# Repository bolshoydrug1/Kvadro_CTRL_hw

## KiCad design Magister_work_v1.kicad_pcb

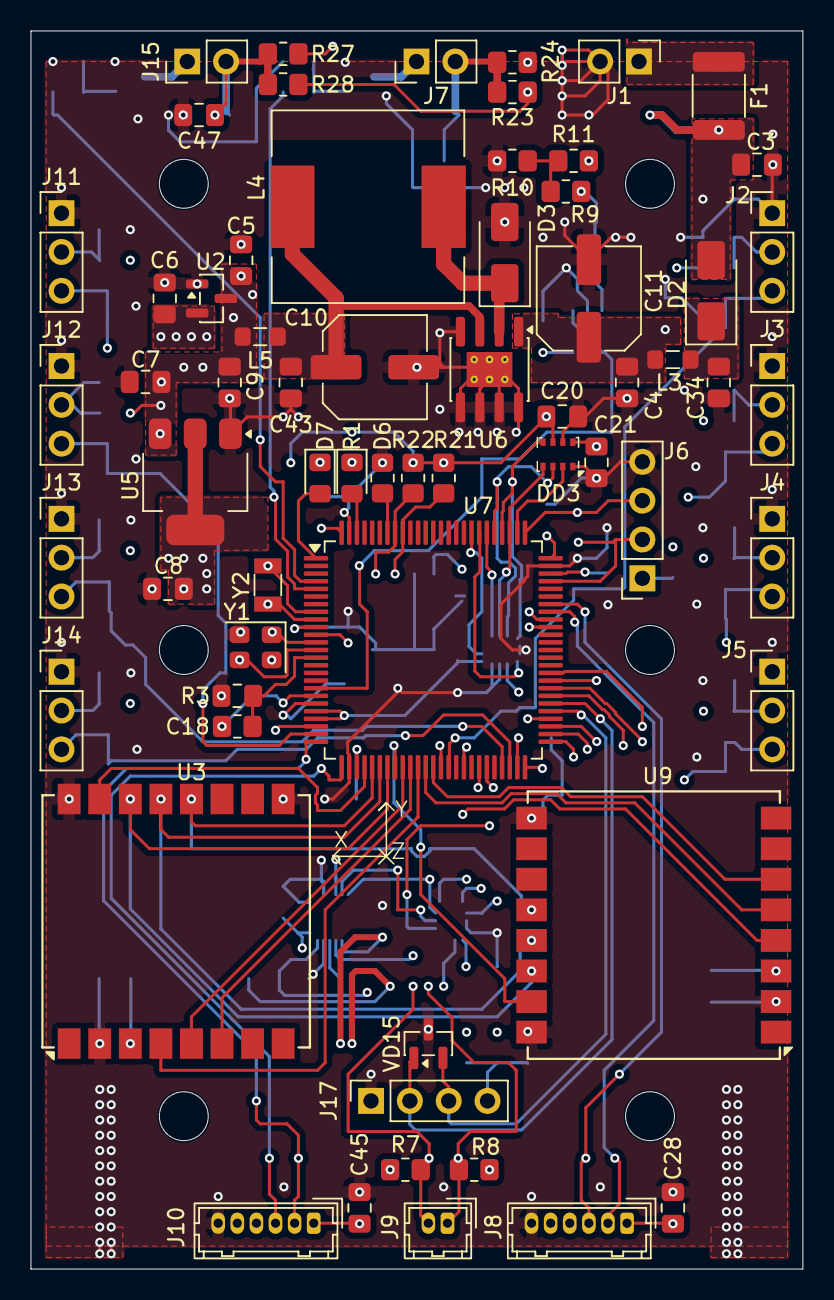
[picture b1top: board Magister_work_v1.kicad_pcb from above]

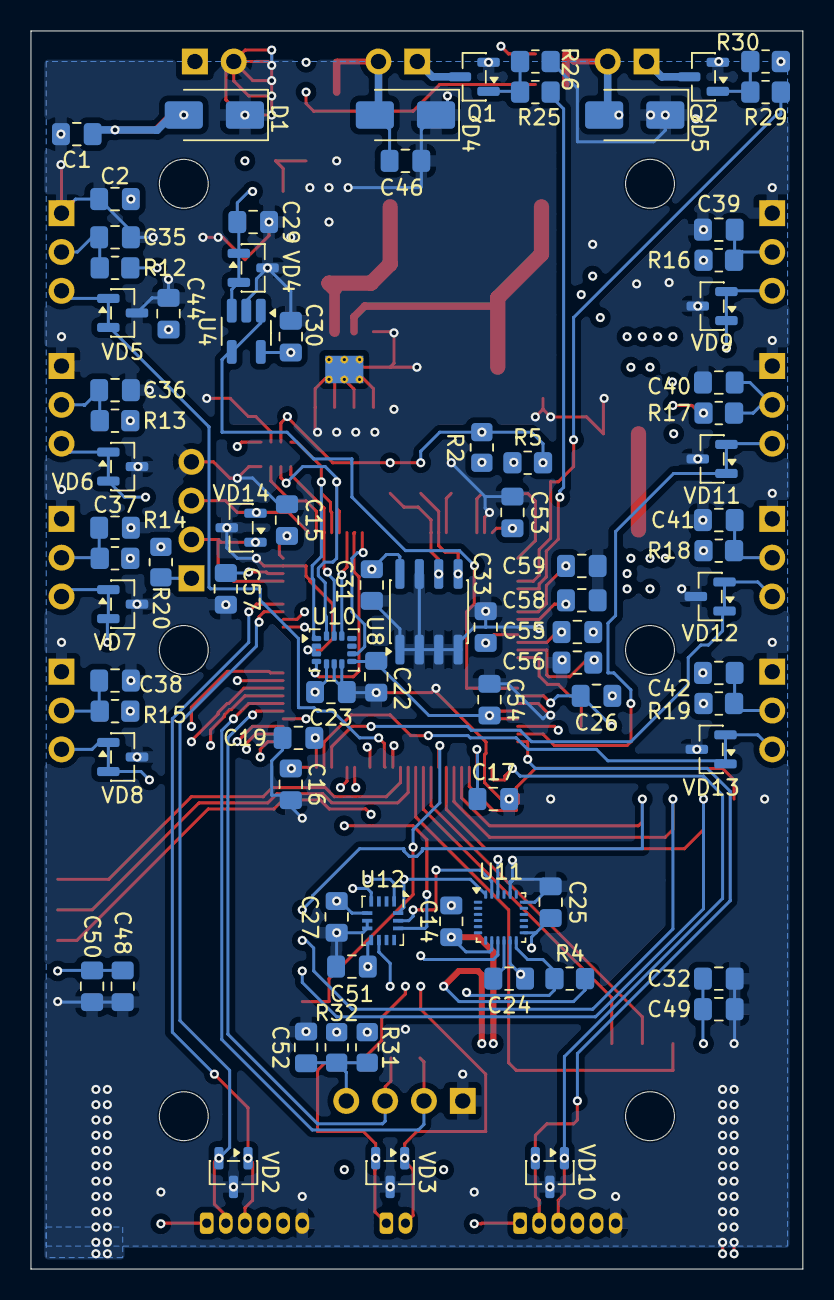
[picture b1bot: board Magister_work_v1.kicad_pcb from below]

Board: 4 copper layers, 50.5 x 81.0 mm, 145 parts (81 on the bottom side), 90 nets.

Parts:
C1: 0.01u; C_0805_2012Metric_Pad1.18x1.45mm_HandSolder
C2, C4, C5, C6, C7, C8, C9, C14, C15, C16, C17, C18, C20, C21, C22, C23, C24, C25, C26, C27, C28, C29, C30, C31, C32, C33, C34, C35, C36, C37, C38, C39, C40, C41, C42, C43, C44, C45, C46, C47, C48, C49, C50, C51, C52, C53, C54: 0.1u; C_0805_2012Metric_Pad1.18x1.45mm_HandSolder
C3: 1u; C_0805_2012Metric_Pad1.18x1.45mm_HandSolder
C10, C11: 100u; C_Elec_6.3x7.7
C19, C57: 2.2u; C_0805_2012Metric_Pad1.18x1.45mm_HandSolder
C55, C56, C58, C59: 15p; C_0805_2012Metric_Pad1.18x1.45mm_HandSolder
D1, D4, D5: SMAJ30CA; D_SMA
D2, D3: SS36; D_SMA
D6, D7: LED; LED_0805_2012Metric_Pad1.15x1.40mm_HandSolder
DD3: BMP280; Bosch_LGA-8_2x2.5mm_P0.65mm_ClockwisePinNumbering
F1: MF-MSMF110-2; Fuse_1812_4532Metric_Pad1.30x3.40mm_HandSolder
J1, J7, J15: Conn_01x02_Pin; PinHeader_1x02_P2.54mm_Vertical
J2, J3, J4, J5, J11, J12, J13, J14: Conn_01x03_Pin; PinHeader_1x03_P2.54mm_Vertical
J6, J17: Conn_01x04_Pin; PinSocket_1x04_P2.54mm_Vertical
J8, J10: Conn_01x06_Pin; Hirose_DF13-06P-1.25DSA_1x06_P1.25mm_Vertical
J9: Conn_01x02_Pin; Hirose_DF13-02P-1.25DSA_1x02_P1.25mm_Vertical
L3, L5: BLM21PG121SN1D; L_0805_2012Metric_Pad1.05x1.20mm_HandSolder
L4: 47uH; L_12x12mm_H8mm
Q1, Q2: AO3400A; SOT-23
R1, R3, R4, R11, R26, R30: 10k; R_0805_2012Metric_Pad1.20x1.40mm_HandSolder
R2, R5: 330; R_0805_2012Metric_Pad1.20x1.40mm_HandSolder
R7, R8, R9, R21, R22: 3k; R_0805_2012Metric_Pad1.20x1.40mm_HandSolder
R10: 1k; R_0805_2012Metric_Pad1.20x1.40mm_HandSolder
R12, R13, R14, R15, R16, R17, R18, R19, R20, R23, R24, R27, R28, R31, R32: 0; R_0805_2012Metric_Pad1.20x1.40mm_HandSolder
R25, R29: 100; R_0805_2012Metric_Pad1.20x1.40mm_HandSolder
U2: XC6206P332MR; SOT-23
U3: Ai-Thinker-Ra-01; Ai-Thinker-Ra-01-LoRa
U4: MCP6001-OT; SOT-23-5_HandSoldering
U5: AMS1117-3.3; SOT-223-3_TabPin2
U6: XL1509-5.0; SOIC-8-1EP_3.9x4.9mm_P1.27mm_EP2.29x3mm_ThermalVias
U7: STM32F407VETx; LQFP-100_14x14mm_P0.5mm
U8: AT24C256; SOIC-8_3.9x4.9mm_P1.27mm
U9: Ai-Thinker-Ra-01SH; Ai-Thinker-Ra-01-LoRa
U10: LSM6DS3; LGA-14_3x2.5mm_P0.5mm_LayoutBorder3x4y
U11: MPU-6500; InvenSense_QFN-24_3x3mm_P0.4mm
U12: BMI270; Bosch_LGA-14_3x2.5mm_P0.5mm
VD2, VD3, VD4, VD5, VD6, VD7, VD8, VD9, VD10, VD11, VD12, VD13, VD14, VD15: GSOT03C-E3-08; SOT-23
Y1: X322525MQB4SI; Oscillator_SMD_Abracon_ASE-4Pin_3.2x2.5mm
Y2: SMD03215C2; Crystal_SMD_3215-2Pin_3.2x1.5mm

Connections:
+3V3A: C6.1, C21.1, C22.1, C25.1, C30.1, C51.2, C54.2, DD3.8 (VDD), U2.2 (VO), U4.5 (V+), U7.21 (VREF+), U7.22 (VDDA), U10.8 (VDD), U11.13 (VDD), U12.8 (VDD)
+3V3D: C8.1, C14.1, C15.1, C16.1, C17.1, C20.1, C23.2, C26.1, C27.1, C31.1, C32.1, C33.1, C48.1, C49.1, C50.1, C53.1, DD3.6 (VDDIO), R2.2, R3.1, R4.2, R5.2, R7.1, R8.1, R20.1, R21.1, R22.1, R31.1, U3.3 (VDD), U5.2 (VO), U7.6 (VBAT), U7.11 (VDD), U7.19 (VDD), U7.28 (VDD), U7.50 (VDD), U7.75 (VDD), U7.100 (VDD), U8.8 (VCC), U9.3 (VDD), U10.5 (VDDIO), U11.8 (VDDIO), U12.5 (VDDIO)
+5V: C5.1, C7.1, C9.1, C28.1, C45.1, J8.1, J10.1, L5.2, R12.2, R13.2, R14.2, R15.2, R16.2, R17.2, R18.2, R19.2, R24.1, R27.1, R32.1, U2.3 (VI), U5.3 (VI)
+12V: C4.1, C11.1, C44.1, L3.2, R9.1, R23.1, R28.1, U6.1 (VIN)
+12V_1: F1.1 (A1), J1.1
+12V_in: C1.1, C2.1, C3.1, D1.2 (A2), D2.2 (A), F1.2 (A2)
/STMF401_Sheet/BOOT0: R1.1, U7.94 (BOOT0)
/STMF401_Sheet/HSE_IN: C55.2, U7.12 (PH0), Y1.1 (OSC)
/STMF401_Sheet/HSE_OUT: C56.1, U7.13 (PH1), Y1.3 (OSC)
/STMF401_Sheet/LSE_IN: C59.1, U7.8 (PC14), Y2.2 (OSC)
/STMF401_Sheet/LSE_OUT: C58.2, U7.9 (PC15), Y2.1 (OSC)
/STMF401_Sheet/RST: C18.1, R3.2, U7.14 (NRST)
/STMF401_Sheet/SWCLK: J6.3, U7.76 (PA14), VD14.2 (K2)
/STMF401_Sheet/SWDIO: J6.2, U7.72 (PA13), VD14.1 (K1)
/STMF401_Sheet/VCAP1: C19.1, U7.49 (VCAP_1)
/STMF401_Sheet/VCAP2: C57.1, U7.73 (VCAP_2)
BAT_CTRL: U4.1, U4.4 (-), U7.18 (PC3)
BMI270_CS: U7.51 (PB12), U12.12 (CSB)
BMI270_INT1: U7.57 (PD10), U12.4 (INT1)
BMI270_INT2: U7.58 (PD11), U12.9 (INT2)
BMI270_SCLK: U7.52 (PB13), U11.23 (SCL/SCLK), U12.13 (SCx)
BMI270_SDI: U7.54 (PB15), U11.24 (SDA/SDI), U12.14 (SDx)
BMI270_SDO: U7.53 (PB14), U11.9 (AD0/SDO), U12.1 (SDO)
BN_880_RX: J8.3, U7.69 (PA10), VD2.1 (K1)
BN_880_SCL: J9.2, R7.2, U7.67 (PA8), VD3.1 (K1)
BN_880_SDA: J9.1, R8.2, U7.66 (PC9), VD3.2 (K2)
BN_880_TX: J8.2, U7.68 (PA9), VD2.2 (K2)
CSB_BMP280: DD3.2 (CSB), U7.77 (PA15)
DEBUG_RX1: J10.3, U7.26 (PA3), VD10.1 (K1)
DEBUG_RX2: J17.2, U7.56 (PD9), VD15.1 (K1)
DEBUG_TX1: J10.2, U7.25 (PA2), VD10.2 (K2)
DEBUG_TX2: J17.3, U7.55 (PD8), VD15.2 (K2)
DIO0_LoRa: U3.5 (DIO0), U7.34 (PC5)
DIO0_RaSH: U7.37 (PB2), U9.5 (DIO0)
DIO1_LoRa: U3.6 (DIO1), U7.35 (PB0)
DIO1_RaSH: U7.38 (PE7), U9.6 (DIO1)
EEPROM_SCL: R21.2, U7.92 (PB6), U8.6 (SCL)
EEPROM_SDA: R22.2, U7.93 (PB7), U8.5 (SDA)
GND: C1.2, C2.2, C3.2, C4.2, C5.2, C6.2, C7.2, C8.2, C9.2, C10.2, C11.2, C14.2, C15.2, C16.2, C17.2, C18.2, C19.2, C20.2, C21.2, C22.2, C23.1, C24.2, C25.2, C26.2, C27.2, C28.2, C29.2, C30.2, C31.2, C32.2, C33.2, C34.2, C35.1, C36.1, C37.1, C38.1, C39.1, C40.1, C41.1, C42.1, C43.2, C44.2, C45.2, C46.2, C47.2, C48.2, C49.2, C50.2, C51.1, C52.2, C53.2, C54.1, C55.1, C56.2, C57.2, C58.1, C59.2, D1.1 (A1), D3.2 (A), D4.1 (A1), D5.1 (A1), DD3.1 (GND), DD3.7 (GND), J1.2, J2.1, J3.1, J4.1, J5.1, J6.4, J8.6, J10.6, J11.1, J12.1, J13.1, J14.1, J17.1, Q1.2 (S), Q2.2 (S), R1.2, R10.2, R26.2, R30.2, U2.1 (GND), U3.2 (GND), U3.9 (GND), U3.16 (GND), U4.2 (V-), U5.1 (GND), U6.4 (~EN), U6.5 (GND), U6.6 (GND), U6.7 (GND), U6.8 (GND), U6.9, U7.10 (VSS), U7.20 (VSSA), U7.27 (VSS), U7.74 (VSS), U7.99 (VSS), U8.1 (A0), U8.2 (A1), U8.3 (A2), U8.4 (GND), U8.7 (WP), U9.2 (GND), U9.9 (GND), U9.16 (GND), U10.2 (SDX), U10.3 (SCX), U10.6 (GND), U10.7 (GND), U11.11 (FSYNC), U11.18 (GND), U11.20 (RESV_GND), U12.6 (GNDIO), U12.7 (GND), VD2.3 (A), VD3.3 (A), VD4.3 (A), VD5.3 (A), VD6.3 (A), VD7.3 (A), VD8.3 (A), VD9.3 (A), VD10.3 (A), VD11.3 (A), VD12.3 (A), VD13.3 (A), VD14.3 (A), VD15.3 (A), Y1.2 (GND), Y1.4 (GND)
LSM_CS: U7.81 (PD0), U10.12 (CS)
LSM_INT1: U7.82 (PD1), U10.4 (INT1)
LSM_INT2: U7.83 (PD2), U10.9 (INT2)
LSM_SCLK: DD3.4 (SCK), U7.78 (PC10), U10.13 (SCL)
LSM_SDI: DD3.3 (SDI), U7.80 (PC12), U10.14 (SDA)
LSM_SDO: DD3.5 (SDO), U7.79 (PC11), U10.1 (SDO/SA0)
MISO_LoRa: U3.13 (MISO), U7.31 (PA6), U9.13 (MISO)
MOSI_LoRa: U3.14 (MOSI), U7.32 (PA7), U9.14 (MOSI)
MPU_CS: U7.59 (PD12), U11.22 (~CS)
MPU_INT: R4.1, U7.60 (PD13), U11.12 (INT)
unnamed: C34.1, D2.1 (K), L3.1
unnamed: D3.1 (K), L4.1, U6.2 (OUT)
unnamed: C46.1, D4.2 (A2), J7.2, R23.2, R24.2
unnamed: C47.1, D5.2 (A2), J15.2, R27.2, R28.2
unnamed: D6.2 (A), U7.98 (PE1)
unnamed: D6.1 (K), R2.1
unnamed: D7.2 (A), U7.1 (PE2)
unnamed: D7.1 (K), R5.1
unnamed: C35.2, J2.2, R12.1
unnamed: C36.2, J3.2, R13.1
unnamed: C37.2, J4.2, R14.1
unnamed: C38.2, J5.2, R15.1
unnamed: J6.1, R20.2
unnamed: J7.1, Q1.3 (D)
unnamed: C39.2, J11.2, R16.1
unnamed: C40.2, J12.2, R17.1
unnamed: C41.2, J13.2, R18.1
unnamed: C42.2, J14.2, R19.1
unnamed: J15.1, Q2.3 (D)
unnamed: C52.1, J17.4, R31.2, R32.2
unnamed: Q1.1 (G), R25.2, R26.1
unnamed: Q2.1 (G), R29.2, R30.1
unnamed: R9.2, R10.1, R11.1
unnamed: C29.1, R11.2, U4.3 (+), VD4.1 (K1), VD4.2 (K2)
unnamed: C10.1, C43.1, L4.2, L5.1, U6.3 (FB)
unnamed: C24.1, U11.10 (REGOUT)
POWER_DO1: R25.1, U7.5 (PE6)
POWER_DO2: R29.1, U7.4 (PE5)
PWM1: J2.3, U7.40 (PE9), VD5.1 (K1), VD5.2 (K2)
PWM2: J3.3, U7.42 (PE11), VD6.1 (K1), VD6.2 (K2)
PWM3: J4.3, U7.44 (PE13), VD7.1 (K1), VD7.2 (K2)
PWM4: J5.3, U7.45 (PE14), VD8.1 (K1), VD8.2 (K2)
PWM5: J11.3, U7.23 (PA0), VD9.1 (K1), VD9.2 (K2)
PWM6: J12.3, U7.24 (PA1), VD11.1 (K1), VD11.2 (K2)
PWM7: J13.3, U7.47 (PB10), VD12.1 (K1), VD12.2 (K2)
PWM8: J14.3, U7.48 (PB11), VD13.1 (K1), VD13.2 (K2)
Reset_LoRa: U3.4 (~RESET), U7.36 (PB1)
Reset_RaSH: U7.39 (PE8), U9.4 (~RESET)
SCK_LoRa: U3.12 (SCK), U7.30 (PA5), U9.12 (SCK)
SS_LoRa: U3.15 (~NSS), U7.29 (PA4)
SS_RaSH: U7.33 (PC4), U9.15 (~NSS)

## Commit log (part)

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2026-05-18 feat: added scheme of power and MCU
2026-05-19 feat: added connection for sensors
2026-05-22 feat: firs complete version schemattic
2026-05-23 feat: added UART for debug
2026-05-23 feat: Added part of the connections (digital data lines) of the microcontroller
2026-05-24 feat: added all connection for MCU
2026-05-28 feat: complete schematic, and start PCB
2026-05-29 feat: first version pf PCB without data and power line
2026-05-30 feat: start PCB trace
2026-05-30 feat: replace MPU6050 perefery
2026-05-31 feat: added line for 5V power
2026-06-01 feat: added 3.3V line Power for Lora and sensors
2026-06-02 feat: added power lines for MCU
2026-06-02 fix: fix bug with locked hole
2026-06-04 feat: added MPU and PWM line
2026-06-05 feat: added mani lines for GND
2026-06-06 feat: add zone for 3v3D power
2026-06-07 feat: added zone for GND and 3v3A
2026-06-07 feat: first version complitr PCB
2026-06-07 feat: added gbr files
